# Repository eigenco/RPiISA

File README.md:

# RPiISA
Raspberry Pi to ISA bus, including Adlib emulation and PCB

Emulator to ISA (e.g. VGA-adapter), i.e. files in the directories beginning 20231105, correspond to this video: 

https://www.youtube.com/watch?v=V3mTAtPauRs

Portions of the emulator code are from this project: https://github.com/adriancable/8086tiny

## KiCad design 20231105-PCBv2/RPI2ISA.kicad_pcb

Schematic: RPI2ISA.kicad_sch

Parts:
J1: Bus_ISA_8bit; BUS_PC
J2: Raspberry_Pi_2_3; PinHeader_2x20_P2.54mm_Vertical
J3: Conn_02x10_Counter_Clockwise; DIP-20_W7.62mm_Socket
Y1: ACH-14.31818MHZ-EK; ACH16000MHZEK; Mouser Part Number 815-ACH-14.31818EK

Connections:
A0: J1.62 (BA00), J2.40 (GPIO21/SCLK1), J3.2
A1: J1.61 (BA01), J2.38 (GPIO20/MOSI1), J3.3
A2: J1.60 (BA02), J2.37 (GPIO26), J3.4
A3: J1.59 (BA03), J2.36 (GPIO16), J3.5
A4: J1.58 (BA04), J2.35 (GPIO19/MISO1), J3.6
A5: J1.57 (BA05), J2.33 (PWM1/GPIO13), J3.7
A6: J1.56 (BA06), J2.32 (PWM0/GPIO12), J3.8
A7: J1.55 (BA07), J2.31 (GCLK2/GPIO6), J3.9
A8: J1.54 (BA08), J2.29 (GCLK1/GPIO5)
A9: J1.53 (BA09), J2.28 (ID_SC/GPIO1)
A10: J1.52 (BA10), J2.27 (ID_SD/GPIO0)
A11: J1.51 (BA11), J2.26 (~CE1/GPIO7)
A12: J1.50 (BA12), J3.19
A13: J1.49 (BA13), J3.18
A14: J1.48 (BA14), J3.17
A15: J1.47 (BA15), J3.16
A16: J1.46 (BA16), J3.15
A17: J1.45 (BA17), J3.14
A18: J1.44 (BA18), J3.13
A19: J1.43 (BA19), J3.12
D0: J1.40 (DB0), J2.13 (GPIO27)
D1: J1.39 (DB1), J2.12 (GPIO18/PWM0)
D2: J1.38 (DB2), J2.11 (GPIO17)
D3: J1.37 (DB3), J2.10 (GPIO15/RXD)
D4: J1.36 (DB4), J2.8 (GPIO14/TXD)
D5: J1.35 (DB5), J2.7 (GCLK0/GPIO4)
D6: J1.34 (DB6), J2.5 (SCL/GPIO3)
D7: J1.33 (DB7), J2.3 (SDA/GPIO2)
GND: J1.1 (GND), J1.10 (GND), J1.31 (GND), J1.42 (AEN), J2.6 (GND), J2.9 (GND), J2.14 (GND), J2.20 (GND), J2.25 (GND), J2.30 (GND), J2.34 (GND), J2.39 (GND), J3.1, J3.10, Y1.4
IOR: J1.14 (~IOR), J2.23 (SCLK0/GPIO11)
IOW: J1.13 (~IOW), J2.22 (GPIO25)
LA: J2.16 (GPIO23), J3.11
MEMR: J1.12 (~SMEMR), J2.21 (MISO0/GPIO9)
MEMW: J1.11 (~SMEMW), J2.19 (MOSI0/GPIO10)
OSC: J1.30 (OSC), Y1.5
READY: J1.41 (IO_READY), J2.18 (GPIO24)
RESET: J1.2 (RESET), J2.15 (GPIO22)
VCC: J1.3 (VCC), J1.29 (VCC), J2.2 (5V), J2.4 (5V), J3.20, Y1.8

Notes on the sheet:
TODO -Add missing pullup (10k) for READY

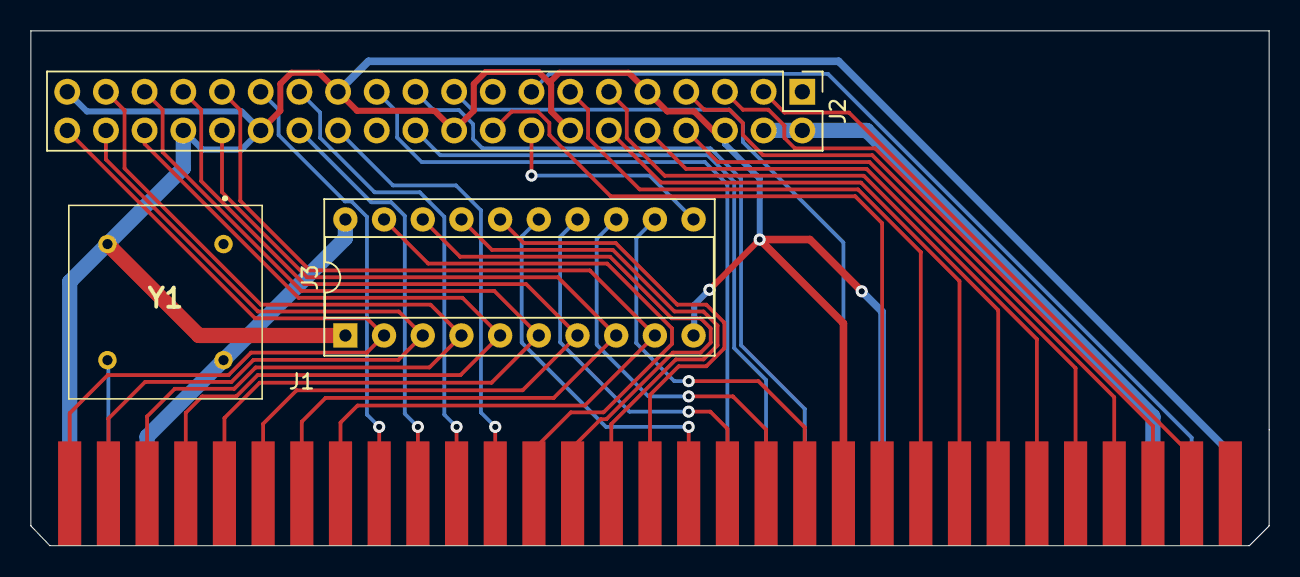
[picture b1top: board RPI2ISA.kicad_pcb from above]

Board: 2 copper layers, 81.3 x 33.8 mm, 4 parts (0 on the bottom side), 38 nets.

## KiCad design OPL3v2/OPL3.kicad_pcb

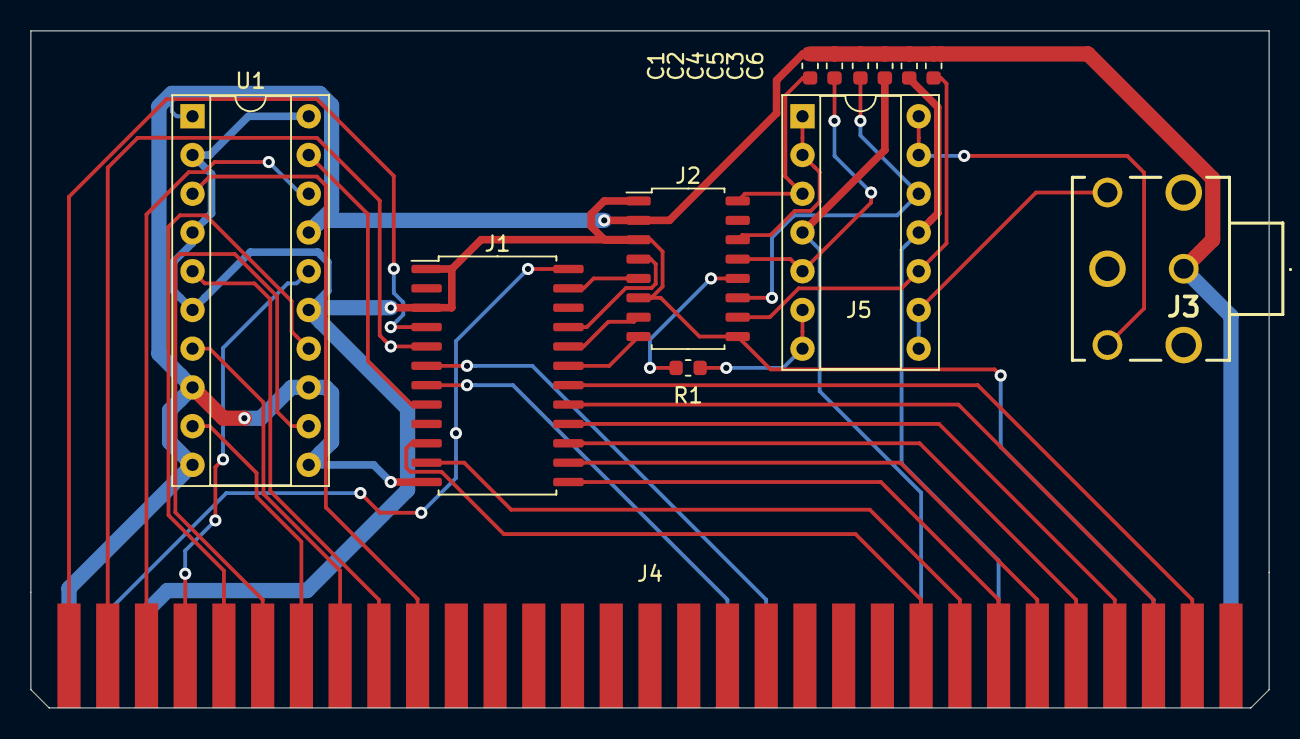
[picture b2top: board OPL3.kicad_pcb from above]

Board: 2 copper layers, 81.2 x 44.4 mm, 13 parts (0 on the bottom side), 39 nets.

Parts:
C1, C5, C6: 10uF; C_0603_1608Metric
C2: 52pF; C_0603_1608Metric
C3, C4: 2.7nF; C_0603_1608Metric
J1: Conn_02x12_Counter_Clockwise; SOP-24_7.5x15.4mm_P1.27mm
J2: Conn_02x08_Counter_Clockwise; SOP-16_4.55x10.3mm_P1.27mm
J3: Conn_02x03_Counter_Clockwise; STX31003N
J4: Bus_ISA_8bit; BUS_PC
J5: Conn_02x07_Counter_Clockwise; DIP-14_W7.62mm_Socket
R1: 33; R_0603_1608Metric
U1: 74LS688; DIP-20_W7.62mm_Socket

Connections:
A0: J1.4, J4.62
A1: J1.5, J4.61
A2: J4.60, U1.18
A3: J4.59, U1.16
A4: J4.58, U1.14
A5: J4.57, U1.12
A6: J4.56, U1.9
A7: J4.55, U1.7
A8: J4.54, U1.5
A9: J4.53, U1.3
AOUT: C2.1, J2.13, J5.5
CH1: C3.1, J2.10, J5.10
CH2: C4.1, J2.11, J5.12
CV: C1.1, J2.16, J5.3
D0: J1.10, J4.40
D1: J1.11, J4.39
D2: J1.13, J4.38
D3: J1.14, J4.37
D4: J1.15, J4.36
D5: J1.16, J4.35
D6: J1.17, J4.34
D7: J1.18, J4.33
DACCLK: J1.23, J2.5
DOAB: J1.21, J2.4
GND: C1.2, C2.2, C3.2, C4.2, C5.2, C6.1, J1.12, J2.2, J3.1, J4.1, J4.10, J4.31, U1.1, U1.8, U1.10, U1.11, U1.13, U1.17
MP: J2.14, J5.1, J5.2
OSC: J1.24, J4.30
OUT2: J5.6, J5.7, R1.2
OUT3: J3.2, J5.8, J5.9
OUT4: J3.5, J5.13, J5.14
SMPAC: J1.20, J2.7
SMPBD: J1.19, J2.8
SWIN: J2.12, R1.1
VCC: J1.1, J1.3, J2.1, J2.3, J2.6, J2.9, J4.3, J4.29, U1.2, U1.4, U1.6, U1.15, U1.20
VM: C6.2, J4.7, J5.11
VP: C5.1, J4.9, J5.4
~CS: J1.8, U1.19
~IOR: J1.7, J4.14
~IOW: J1.6, J4.13

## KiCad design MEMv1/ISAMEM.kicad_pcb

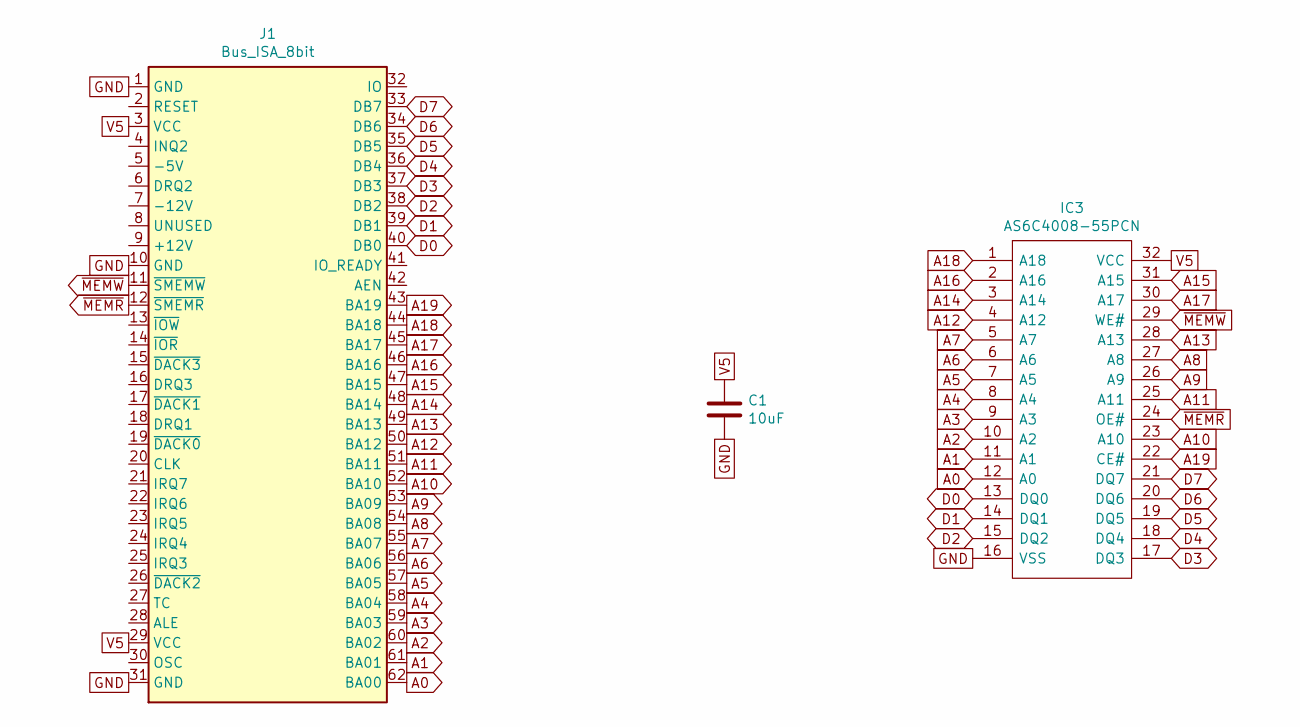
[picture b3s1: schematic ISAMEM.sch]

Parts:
C1: 10uF; C_0603_1608Metric
IC3: AS6C4008-55PCN; DIP1524W58P254L4191H406Q32N; Mouser Part Number 913-AS6C4008-55PCN
J1: Bus_ISA_8bit; BUS_PC

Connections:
A0: IC3.12 (A0), J1.62 (BA00)
A1: IC3.11 (A1), J1.61 (BA01)
A2: IC3.10 (A2), J1.60 (BA02)
A3: IC3.9 (A3), J1.59 (BA03)
A4: IC3.8 (A4), J1.58 (BA04)
A5: IC3.7 (A5), J1.57 (BA05)
A6: IC3.6 (A6), J1.56 (BA06)
A7: IC3.5 (A7), J1.55 (BA07)
A8: IC3.27 (A8), J1.54 (BA08)
A9: IC3.26 (A9), J1.53 (BA09)
A10: IC3.23 (A10), J1.52 (BA10)
A11: IC3.25 (A11), J1.51 (BA11)
A12: IC3.4 (A12), J1.50 (BA12)
A13: IC3.28 (A13), J1.49 (BA13)
A14: IC3.3 (A14), J1.48 (BA14)
A15: IC3.31 (A15), J1.47 (BA15)
A16: IC3.2 (A16), J1.46 (BA16)
A17: IC3.30 (A17), J1.45 (BA17)
A18: IC3.1 (A18), J1.44 (BA18)
A19: IC3.22 (CE#), J1.43 (BA19)
D0: IC3.13 (DQ0), J1.40 (DB0)
D1: IC3.14 (DQ1), J1.39 (DB1)
D2: IC3.15 (DQ2), J1.38 (DB2)
D3: IC3.17 (DQ3), J1.37 (DB3)
D4: IC3.18 (DQ4), J1.36 (DB4)
D5: IC3.19 (DQ5), J1.35 (DB5)
D6: IC3.20 (DQ6), J1.34 (DB6)
D7: IC3.21 (DQ7), J1.33 (DB7)
GND: C1.2, IC3.16 (VSS), J1.1 (GND), J1.10 (GND), J1.31 (GND)
V5: C1.1, IC3.32 (VCC), J1.3 (VCC), J1.29 (VCC)
~MEMR: IC3.24 (OE#), J1.12 (~SMEMR)
~MEMW: IC3.29 (WE#), J1.11 (~SMEMW)

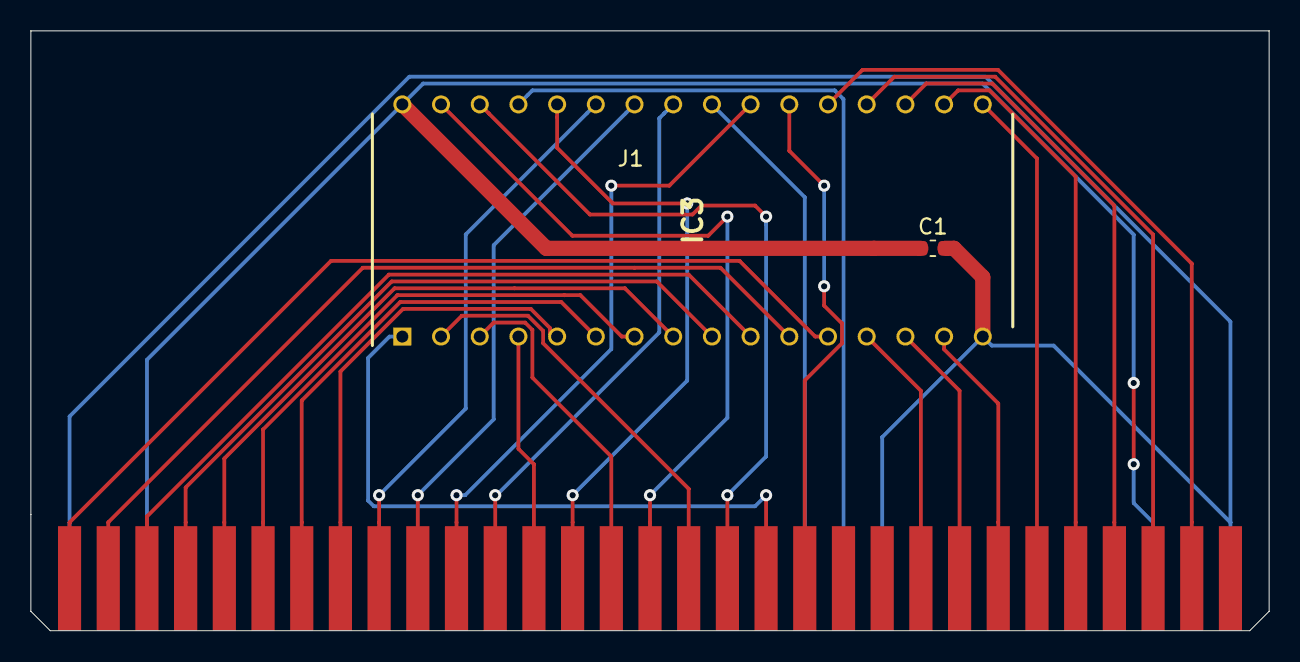
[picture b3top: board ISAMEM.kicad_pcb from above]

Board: 2 copper layers, 81.3 x 39.4 mm, 3 parts (0 on the bottom side), 32 nets.

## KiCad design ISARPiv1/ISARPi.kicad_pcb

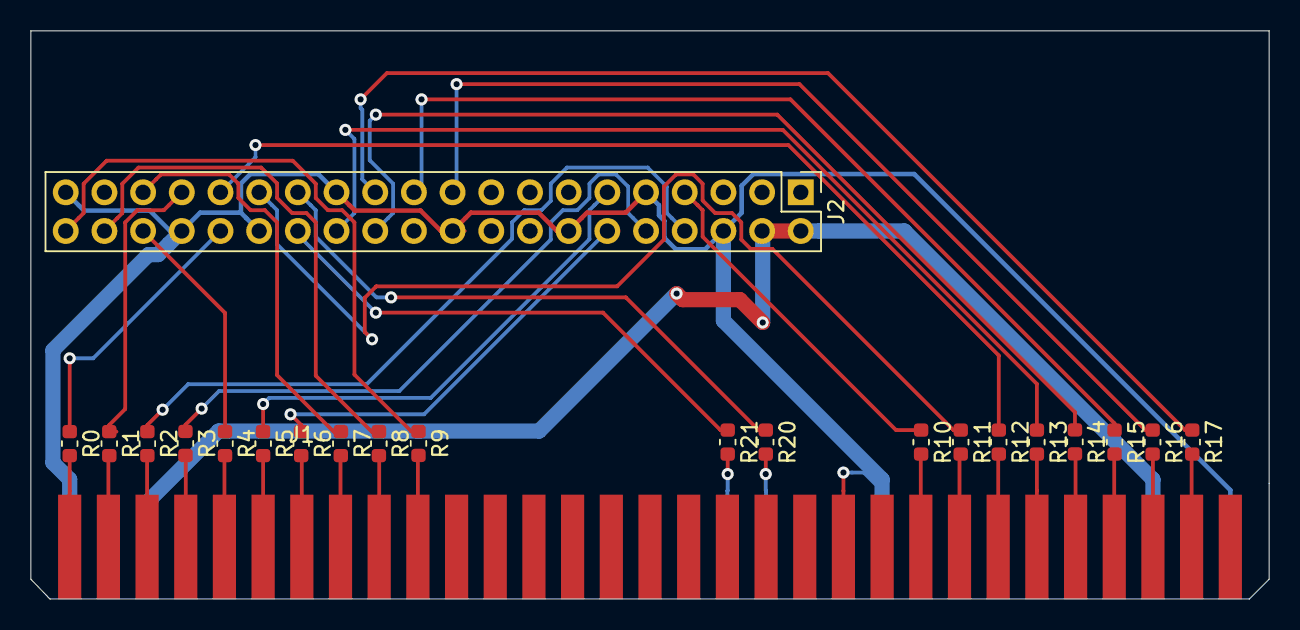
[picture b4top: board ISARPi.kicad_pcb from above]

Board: 2 copper layers, 81.3 x 37.3 mm, 22 parts (0 on the bottom side), 42 nets.

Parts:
J1: Bus_ISA_8bit; BUS_PC
J2: Raspberry_Pi_2_3; PinHeader_2x20_P2.54mm_Vertical
R0, R1, R2, R3, R4, R5, R6, R7, R8, R9, R10, R11, R12, R13, R14, R15, R16, R17, R20, R21: 10; R_0603_1608Metric

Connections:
A0: J1.62, R0.2
A1: J1.61, R1.2
A2: J1.60, R2.2
A3: J1.59, R3.2
A4: J1.58, R4.2
A5: J1.57, R5.2
A6: J1.56, R6.2
A7: J1.55, R7.2
A8: J1.54, R8.2
A9: J1.53, R9.2
D0: J1.40, R10.2
D1: J1.39, R11.2
D2: J1.38, R12.2
D3: J1.37, R13.2
D4: J1.36, R14.2
D5: J1.35, R15.2
D6: J1.34, R16.2
D7: J1.33, R17.2
GND: J1.1, J1.10, J1.31, J1.42, J2.6, J2.9, J2.14, J2.20, J2.25, J2.30, J2.34, J2.39
RA0: J2.32, R0.1
RA1: J2.33, R1.1
RA2: J2.8, R2.1
RA3: J2.10, R3.1
RA4: J2.36, R4.1
RA5: J2.11, R5.1
RA6: J2.12, R6.1
RA7: J2.35, R7.1
RA8: J2.38, R8.1
RA9: J2.40, R9.1
RD0: J2.7, R10.1
RD1: J2.29, R11.1
RD2: J2.31, R12.1
RD3: J2.26, R13.1
RD4: J2.24, R14.1
RD5: J2.21, R15.1
RD6: J2.19, R16.1
RD7: J2.23, R17.1
RnIOR: J2.28, R21.1
RnIOW: J2.27, R20.1
VCC: J1.3, J1.29, J2.2, J2.4
nIOR: J1.14, R21.2
nIOW: J1.13, R20.2

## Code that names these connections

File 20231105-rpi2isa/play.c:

#include <stdio.h>
#include <stdlib.h>
#include <wiringPi.h>
#include <unistd.h>

#define LA 23
#define IOW 25
#define IOR 11
#define MEMR 9
#define MEMW 10
#define RESET 22

#define D0 27
#define D1 18
#define D2 17
#define D3 15
#define D4 14
#define D5 4
#define D6 3
#define D7 2

#define A0 21
#define A1 20
#define A2 26
#define A3 16
#define A4 19
#define A5 13
#define A6 12
#define A7 6
#define A8 5
#define A9 1
#define A10 0
#define A11 7

void setaddr(unsigned short addr) {
  digitalWrite(A0, addr & 1); addr >>= 1;
  digitalWrite(A1, addr & 1); addr >>= 1;
  digitalWrite(A2, addr & 1); addr >>= 1;
  digitalWrite(A3, addr & 1); addr >>= 1;
  digitalWrite(A4, addr & 1); addr >>= 1;
  digitalWrite(A5, addr & 1); addr >>= 1;
  digitalWrite(A6, addr & 1); addr >>= 1;
  digitalWrite(A7, addr & 1); addr >>= 1;
  digitalWrite(A8, addr & 1); addr >>= 1;
  digitalWrite(A9, addr & 1); addr >>= 1;
  digitalWrite(A10, addr & 1); addr >>= 1;
  digitalWrite(A11, addr & 1);
}

void setdata(unsigned char data) {
  digitalWrite(D0, data & 1); data >>= 1;
  digitalWrite(D1, data & 1); data >>= 1;
  digitalWrite(D2, data & 1); data >>= 1;
  digitalWrite(D3, data & 1); data >>= 1;
  digitalWrite(D4, data & 1); data >>= 1;
  digitalWrite(D5, data & 1); data >>= 1;
  digitalWrite(D6, data & 1); data >>= 1;
  digitalWrite(D7, data & 1);
}

unsigned char getdata() {
  unsigned char data;

  data  = digitalRead(D7); data <<= 1;
  data |= digitalRead(D6); data <<= 1;
  data |= digitalRead(D5); data <<= 1;
  data |= digitalRead(D4); data <<= 1;
  data |= digitalRead(D3); data <<= 1;
  data |= digitalRead(D2); data <<= 1;
  data |= digitalRead(D1); data <<= 1;
  data |= digitalRead(D0);

  return data;
}

/*
void setinput() {
  pinMode(D0, INPUT);
  pinMode(D1, INPUT);
  pinMode(D2, INPUT);
  pinMode(D3, INPUT);
  pinMode(D4, INPUT);
  pinMode(D5, INPUT);
  pinMode(D6, INPUT);
  pinMode(D7, INPUT);
}

void setoutput() {
  pinMode(D0, OUTPUT);
  pinMode(D1, OUTPUT);
  pinMode(D2, OUTPUT);
  pinMode(D3, OUTPUT);
  pinMode(D4, OUTPUT);
  pinMode(D5, OUTPUT);
  pinMode(D6, OUTPUT);
  pinMode(D7, OUTPUT);
}
*/

void outb(unsigned short addr, unsigned char data) {
  //setoutput();
  setaddr(addr);
  setdata(data);
  digitalWrite(IOW, 0);
  usleep(1);
  digitalWrite(IOW, 1);
}

void wr_adlib(unsigned char reg, unsigned char value) {
  outb(0x388, reg); usleep(3);
  outb(0x389, value), usleep(22);
}

int main() {
  int i, j, k, x, y, z, song_register, song_data, song_wait, song_offset = 0;
  unsigned char buffer[57306];
  FILE *f;

  f = fopen("lemmings.dat", "rb");
  fread(buffer, 1, 57306, f);
  fclose(f);

  wiringPiSetupGpio();

  pinMode(LA, OUTPUT);
  pinMode(IOW, OUTPUT);
  pinMode(IOR, OUTPUT);
  pinMode(MEMW, OUTPUT);
  pinMode(MEMR, OUTPUT);
  pinMode(RESET, OUTPUT);
  digitalWrite(IOW, 1);
  digitalWrite(IOR, 1);
  digitalWrite(MEMW, 1);
  digitalWrite(MEMR, 1);

  // CONFIGURE ADDRESS PINS
  pinMode(A0, OUTPUT);
  pinMode(A1, OUTPUT);
  pinMode(A2, OUTPUT);
  pinMode(A3, OUTPUT);
  pinMode(A4, OUTPUT);
  pinMode(A5, OUTPUT);
  pinMode(A6, OUTPUT);
  pinMode(A7, OUTPUT);
  pinMode(A8, OUTPUT);
  pinMode(A9, OUTPUT);
  pinMode(A10, OUTPUT);
  pinMode(A11, OUTPUT);

  // CONFIGURE DATA PINS
  pinMode(D0, OUTPUT);
  pinMode(D1, OUTPUT);
  pinMode(D2, OUTPUT);
  pinMode(D3, OUTPUT);
  pinMode(D4, OUTPUT);
  pinMode(D5, OUTPUT);
  pinMode(D6, OUTPUT);
  pinMode(D7, OUTPUT);

  // RESET BUS
  digitalWrite(RESET, 1); usleep(100000);
  digitalWrite(RESET, 0); usleep(100000);

  // PLAY THE LEMMINGS SONG USING ADLIB
  for(;;) {
    song_register = buffer[song_offset];
    song_offset++;
    if(song_register==0) {
      song_wait  = (buffer[song_offset+1] << 8) | buffer[song_offset+0];
      song_offset += 2;
      usleep(1786*song_wait);
    } else {
      song_data = buffer[song_offset]; song_offset++;
      song_wait = buffer[song_offset]; song_offset++;
      wr_adlib(song_register, song_data);
      usleep(1786*song_wait);
    }
    if(song_offset>57300) {
      for(i=0; i<256; i++)
        wr_adlib(i, 0);
      exit(0);
    }
  }

  return 0;
}
